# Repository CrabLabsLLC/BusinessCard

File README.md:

# Crab Labs Business Card

## Author

Orion Serup

## License

[Create Commons Attribution-ShareAlike 4.0](https://creativecommons.org/licenses/by-sa/4.0/)

## Dependencies

To modify or inspect the source you need [KiCad > 8.0](https://www.kicad.org/download/) as well as the KiCad standard library

## Documentation

The specification and additional information can be found [here](/docs/Specification.md)

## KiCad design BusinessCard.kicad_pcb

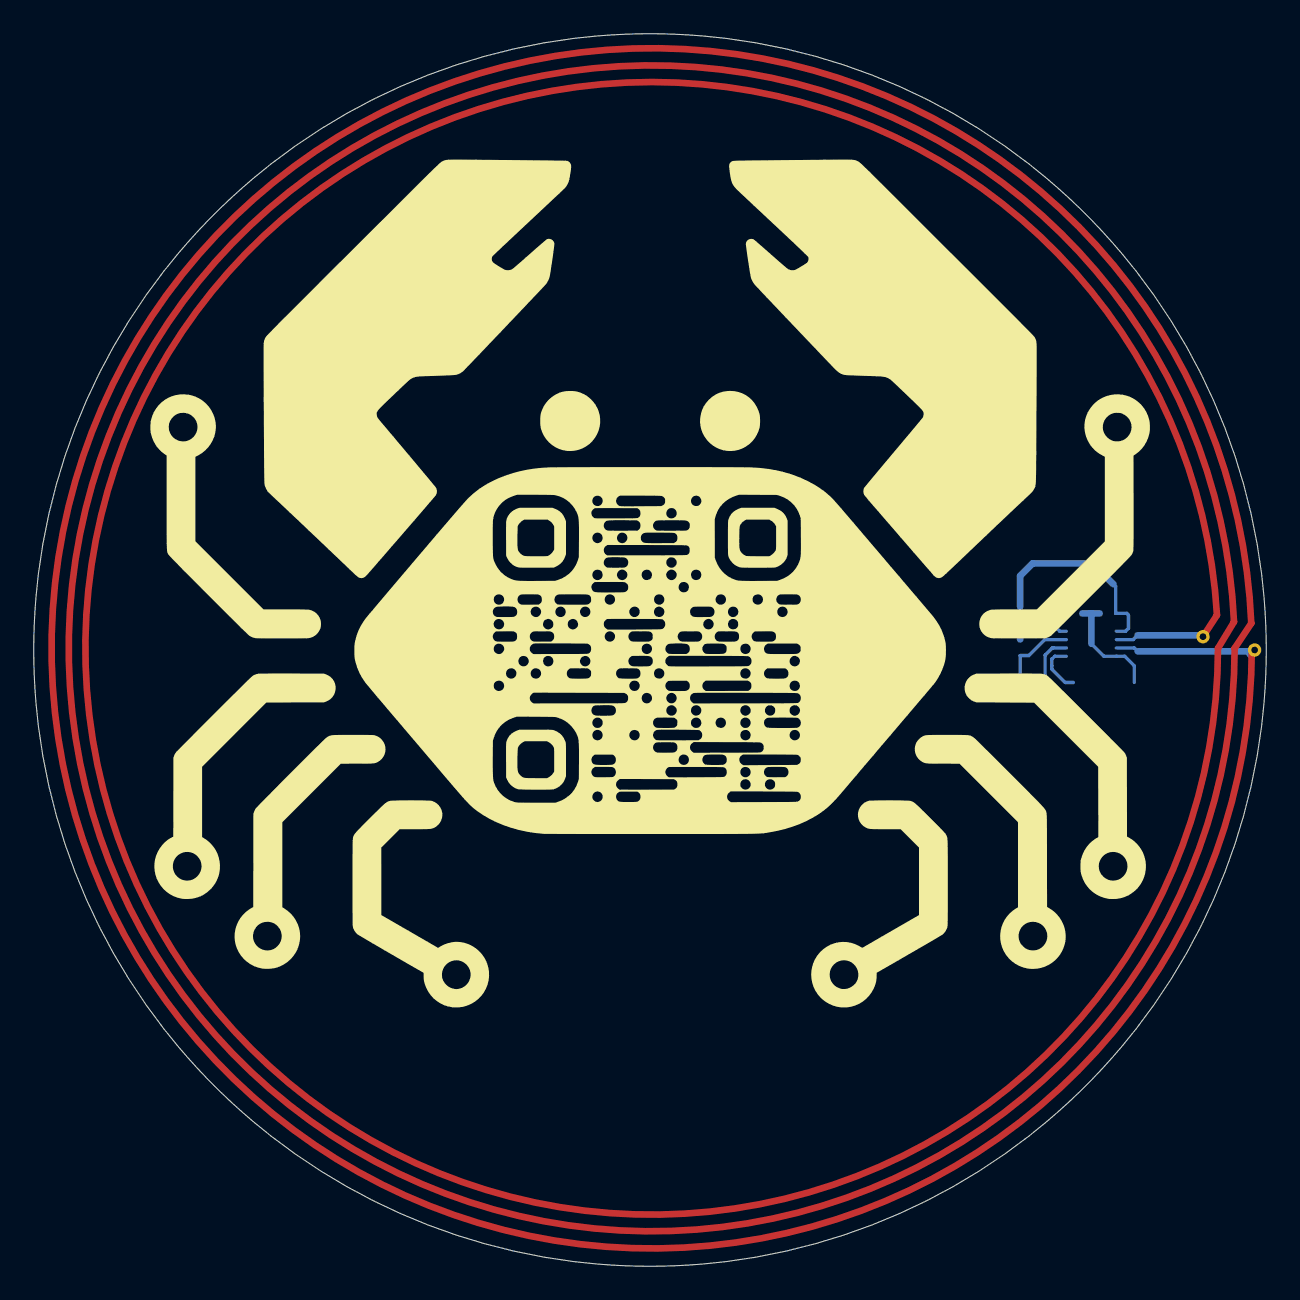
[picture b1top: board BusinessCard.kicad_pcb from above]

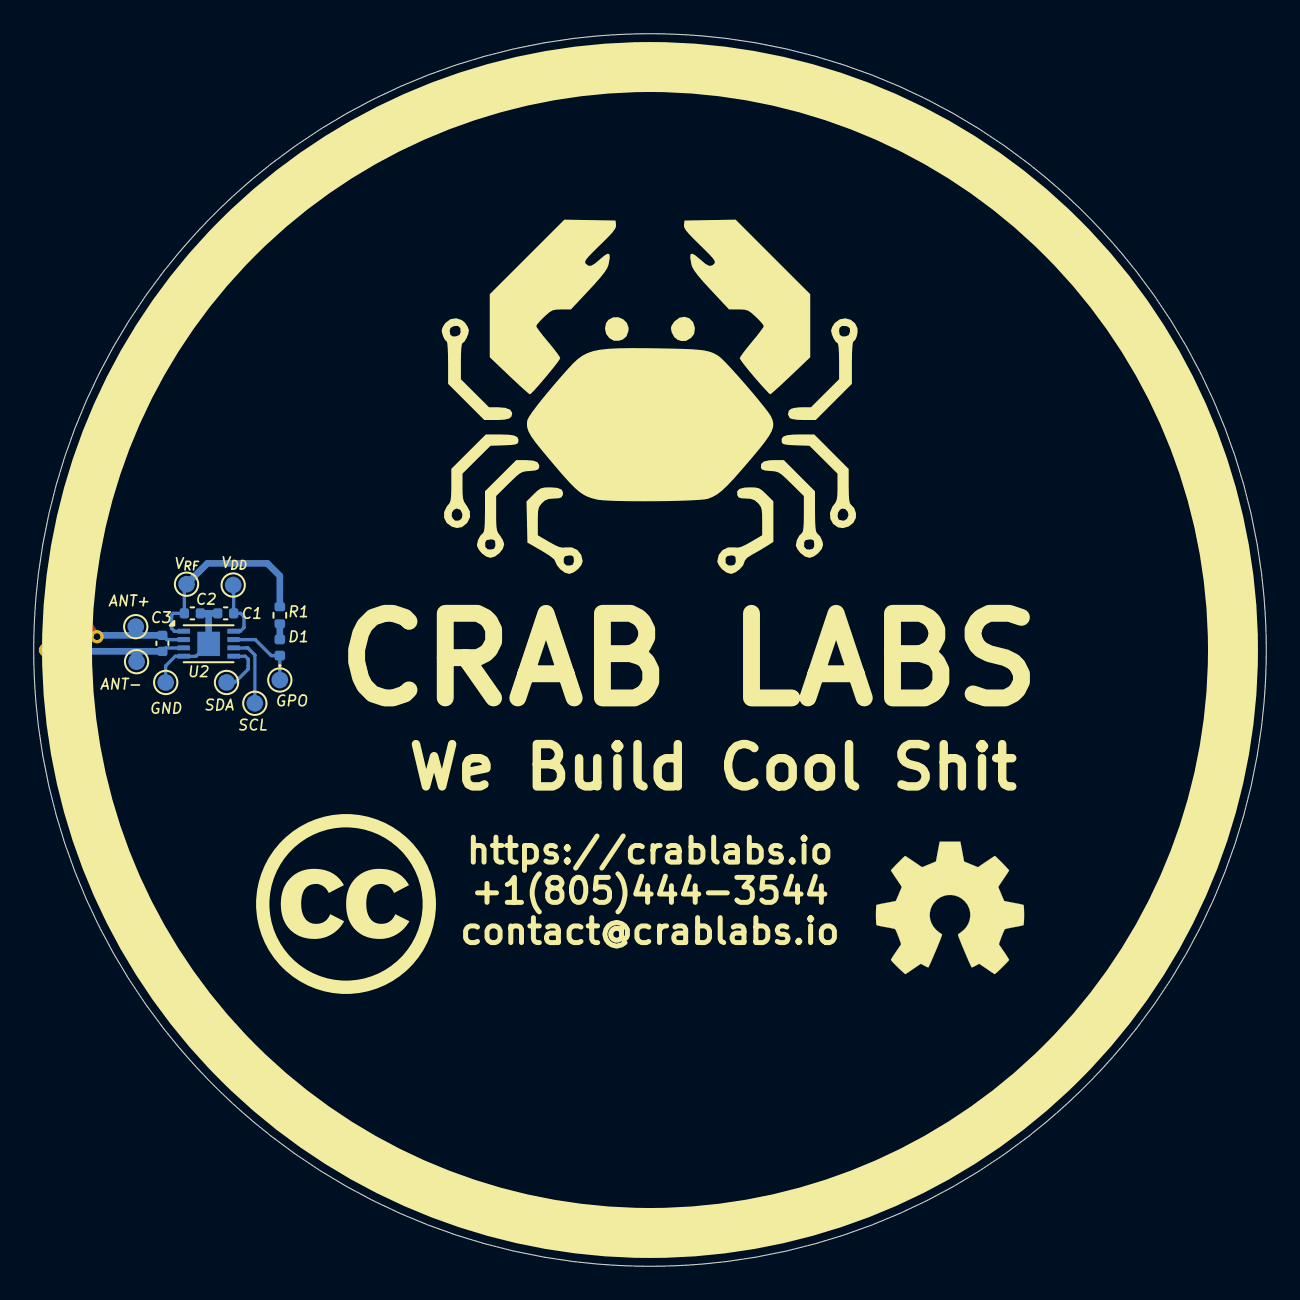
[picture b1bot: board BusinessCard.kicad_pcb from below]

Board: 2 copper layers, 74.0 x 74.0 mm, 15 parts (14 on the bottom side), 9 nets.

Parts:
AE1: NFC Antenna; Antenna
C1, C2: 100nF; C_0402_1005Metric
C3: 39pF; C_0402_1005Metric
D1: Red; LED_0402_1005Metric
R1: 4.7k; R_0402_1005Metric
TP1: SDA; TestPoint_Pad_D1.0mm
TP2: SCL; TestPoint_Pad_D1.0mm
TP3: V_{DD}; TestPoint_Pad_D1.0mm
TP4: GND; TestPoint_Pad_D1.0mm
TP5: GPO; TestPoint_Pad_D1.0mm
TP6: V_{RF}; TestPoint_Pad_D1.0mm
TP7: ANT+; TestPoint_Pad_D1.0mm
TP8: ANT-; TestPoint_Pad_D1.0mm
U2: ST25DV04K; DFN-8-1EP_3x2mm_P0.5mm_EP1.36x1.46mm

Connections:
/ANT+: AE1.2, C3.1, TP7.1, U2.2 (AC0)
/ANT-: AE1.1, C3.2, TP8.1, U2.3 (AC1)
/GND: C1.2, C2.2, TP4.1, U2.4 (VSS)
/GPO: D1.1 (K), TP5.1, U2.7 (GPO)
/SCL: TP2.1, U2.6 (SCL)
/SDA: TP1.1, U2.5 (SDA)
/V_{DD}: C1.1, TP3.1, U2.8 (VCC)
/V_{RF}: C2.1, R1.1, TP6.1, U2.1 (V_EH)
unnamed: D1.2 (A), R1.2

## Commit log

2024-07-13 add images
2024-07-13 added docs

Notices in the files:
BusinessCard.kicad_pcb:
License: CC BY-SA 4.0
